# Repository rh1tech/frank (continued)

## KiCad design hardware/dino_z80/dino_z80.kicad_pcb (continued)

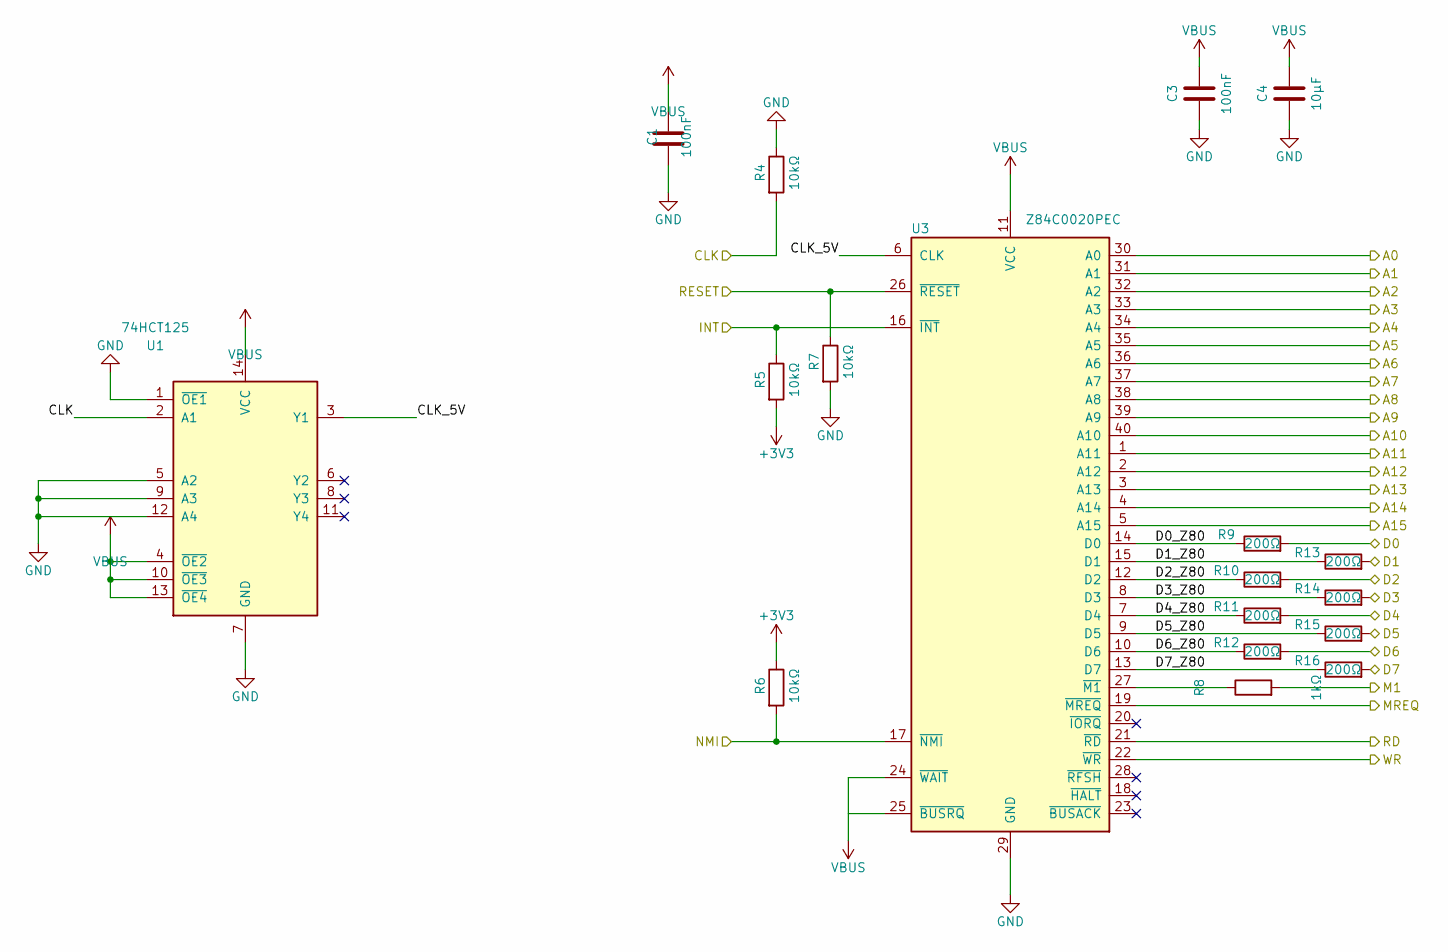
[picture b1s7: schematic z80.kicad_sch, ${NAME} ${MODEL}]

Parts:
C1, C3: 100nF; C_0603_1608Metric
C4: 10µF; C_0603_1608Metric
R4, R5, R6, R7: 10kΩ; R_0603_1608Metric
R8: 1kΩ; R_0603_1608Metric
R9, R10, R11, R12, R13, R14, R15, R16: 200Ω; R_0603_1608Metric
U1: 74HCT125; SOIC127P600X175-14N
U3: Z84C0020PEC; DIP-40_W15.24mm_Socket

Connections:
+3V3: R5.2, R6.1; also elsewhere on the board
/A0: U3.30 (A0); also elsewhere on the board
/A1: U3.31 (A1); also elsewhere on the board
/A2: U3.32 (A2); also elsewhere on the board
/A3: U3.33 (A3); also elsewhere on the board
/A4: U3.34 (A4); also elsewhere on the board
/A5: U3.35 (A5); also elsewhere on the board
/A6: U3.36 (A6); also elsewhere on the board
/A7: U3.37 (A7); also elsewhere on the board
/A8: U3.38 (A8); also elsewhere on the board
/A9: U3.39 (A9); also elsewhere on the board
/A10: U3.40 (A10); also elsewhere on the board
/A11: U3.1 (A11); also elsewhere on the board
/A12: U3.2 (A12); also elsewhere on the board
/A13: U3.3 (A13); also elsewhere on the board
/A14: U3.4 (A14); also elsewhere on the board
/A15: U3.5 (A15); also elsewhere on the board
/CLK: R4.2, U1.2 (A1); also elsewhere on the board
/D0: R9.2; also elsewhere on the board
/D1: R13.2; also elsewhere on the board
/D2: R10.2; also elsewhere on the board
/D3: R14.2; also elsewhere on the board
/D4: R11.2; also elsewhere on the board
/D5: R15.2; also elsewhere on the board
/D6: R12.2; also elsewhere on the board
/D7: R16.2; also elsewhere on the board
/INT: R5.1, U3.16 (~INT); also elsewhere on the board
/M1: R8.2; also elsewhere on the board
/MREQ: U3.19 (~MREQ); also elsewhere on the board
/NMI: R6.2, U3.17 (~NMI); also elsewhere on the board
/RD: U3.21 (~RD); also elsewhere on the board
/RESET: R7.1, U3.26 (~RESET); also elsewhere on the board
/WR: U3.22 (~WR); also elsewhere on the board
/Z80/CLK_5V: U1.3 (Y1), U3.6 (CLK)
/Z80/D0_Z80: R9.1, U3.14 (D0)
/Z80/D1_Z80: R13.1, U3.15 (D1)
/Z80/D2_Z80: R10.1, U3.12 (D2)
/Z80/D3_Z80: R14.1, U3.8 (D3)
/Z80/D4_Z80: R11.1, U3.7 (D4)
/Z80/D5_Z80: R15.1, U3.9 (D5)
/Z80/D6_Z80: R12.1, U3.10 (D6)
/Z80/D7_Z80: R16.1, U3.13 (D7)
GND: C1.2, C3.2, C4.2, R4.1, R7.2, U1.1 (~OE1), U1.5 (A2), U1.7 (GND), U1.9 (A3), U1.12 (A4), U3.29 (GND); also elsewhere on the board
unnamed: R8.1, U3.27 (~M1)
VBUS: C1.1, C3.1, C4.1, U1.4 (~OE2), U1.10 (~OE3), U1.13 (~OE4), U1.14 (VCC), U3.11 (VCC), U3.24 (~WAIT), U3.25 (~BUSRQ); also elsewhere on the board

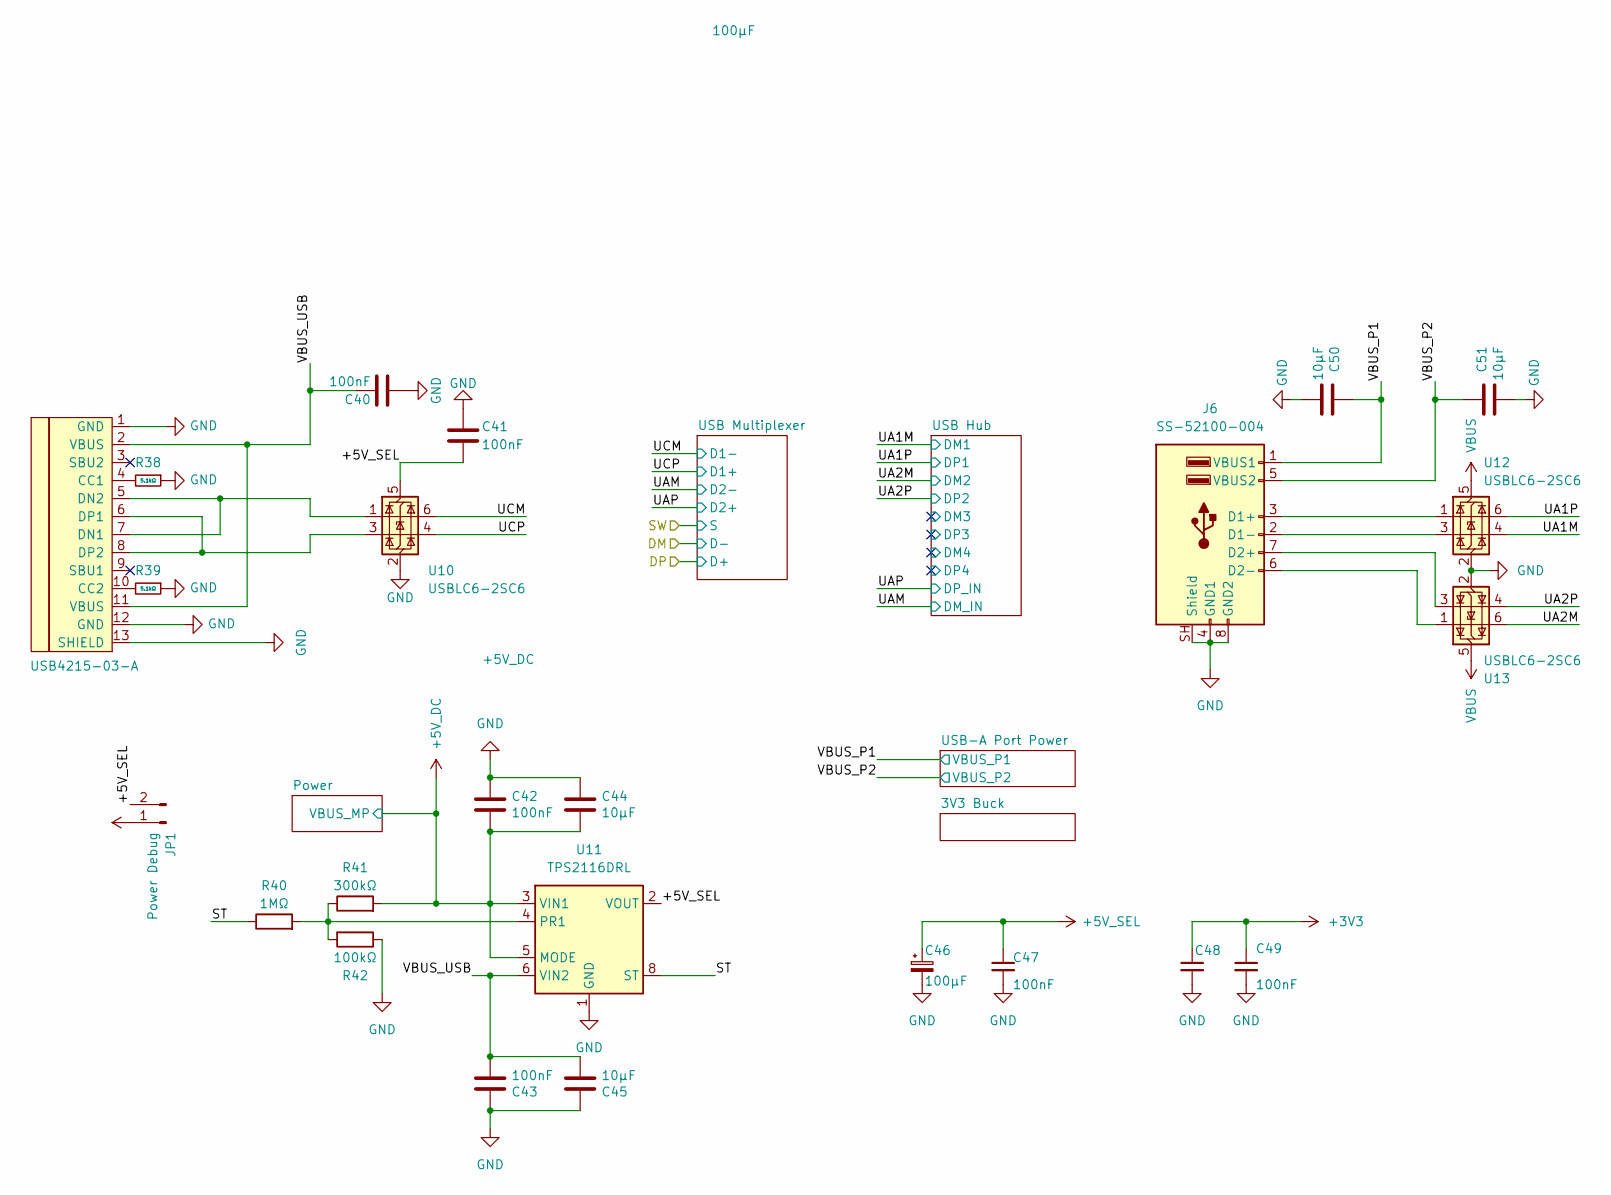
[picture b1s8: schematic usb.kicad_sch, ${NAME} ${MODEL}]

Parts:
C40, C41, C42, C43, C47, C49: 100nF; C_0603_1608Metric
C44, C45, C50, C51: 10µF; C_0603_1608Metric
C46: 100µF; CP_Radial_D6.3mm_P2.50mm
C48: 100µF; C_1206_3216Metric
J5: USB4215-03-A; USB_C_Receptacle; LCSC C165948
J6: SS-52100-004; USB_A_Stacked
JP1: Power Debug; SolderJumper-2_P1.3mm_Open_Pad1.0x1.5mm
R38, R39: 5.1kΩ; R_0603_1608Metric
R40: 1MΩ; R_0603_1608Metric
R41: 300kΩ; R_0603_1608Metric
R42: 100kΩ; R_0603_1608Metric
U10, U12, U13: USBLC6-2SC6; SOT-23-6
U11: TPS2116DRL; SOT-583-8

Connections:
+3V3: C48.1, C49.1; also elsewhere on the board
+5V_DC: C42.2, C44.2, JP1.1, R41.2, U11.3 (VIN1), U11.5 (MODE); also elsewhere on the board
+5V_SEL: C41.2, C46.1, C47.1, JP1.2, U10.5 (VBUS), U11.2 (VOUT), U11.7 (VOUT); also elsewhere on the board
/USB, Power/ST: R40.1, U11.8 (ST)
/USB, Power/UA1M: U12.4 (I/O2); also elsewhere on the board
/USB, Power/UA1P: U12.6 (I/O1); also elsewhere on the board
/USB, Power/UA2M: U13.6 (I/O1); also elsewhere on the board
/USB, Power/UA2P: U13.4 (I/O2); also elsewhere on the board
/USB, Power/UCM: U10.6 (I/O1); also elsewhere on the board
/USB, Power/UCP: U10.4 (I/O2); also elsewhere on the board
/USB, Power/VBUS_P1: C50.1, J6.1 (VBUS1); also elsewhere on the board
/USB, Power/VBUS_P2: C51.1, J6.5 (VBUS2); also elsewhere on the board
/USB, Power/VBUS_USB: C40.1, C43.2, C45.2, J5.2 (VBUS), J5.11 (VBUS), U11.6 (VIN2)
GND: C40.2, C41.1, C42.1, C43.1, C44.1, C45.1, C46.2, C47.2, C48.2, C49.2, C50.2, C51.2, J5.1 (GND), J5.12 (GND), J5.13 (SHIELD), J6.4 (GND1), J6.8 (GND2), J6.SH (Shield), R38.1, R39.1, R42.1, U10.2 (GND), U11.1 (GND), U12.2 (GND), U13.2 (GND); also elsewhere on the board
unnamed: J5.4 (CC1), R38.2
unnamed: J5.10 (CC2), R39.2
unnamed: J5.5 (DN2), J5.7 (DN1), U10.1 (I/O1)
unnamed: J5.6 (DP1), J5.8 (DP2), U10.3 (I/O2)
unnamed: J6.3 (D1+), U12.1 (I/O1)
unnamed: J6.2 (D1-), U12.3 (I/O2)
unnamed: J6.7 (D2+), U13.3 (I/O2)
unnamed: J6.6 (D2-), U13.1 (I/O1)
unnamed: R40.2, R41.1, R42.2, U11.4 (PR1)
VBUS: U12.5 (VBUS), U13.5 (VBUS); also elsewhere on the board

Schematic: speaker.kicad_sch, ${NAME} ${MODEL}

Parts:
C15: 6.8nF; C_0603_1608Metric
C16, C17: 1µF; C_0603_1608Metric
C18: 100nF; C_0603_1608Metric
C19: 10µF; C_0603_1608Metric
C20: 100µF; CP_Radial_D6.3mm_P2.50mm
LS1: CVS-2308
R25, R26: 22kΩ; R_0603_1608Metric
R27: 2kΩ; R_0603_1608Metric
R28, R29, R30: 10kΩ; R_0603_1608Metric
U6: PAM8403D; SOP-16_P1.27mm

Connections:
/Sound/AUDIO_L: R25.1; also elsewhere on the board
/Sound/AUDIO_R: R26.1; also elsewhere on the board
/Sound/SPK_EN: R30.1, U6.12 (SHDN); also elsewhere on the board
/Sound/Speaker/SPK_N: LS1.1 (-), U6.3 (-OUT_L)
/Sound/Speaker/SPK_P: LS1.2 (+), U6.1 (+OUT_L)
GND: C15.2, C17.2, C18.2, C19.2, C20.2, R27.2, R29.2, R30.2, U6.2 (PGND), U6.11 (GND), U6.15 (PGND); also elsewhere on the board
unnamed: C15.1, C16.1, R25.2, R26.2, R27.1
unnamed: C16.2, R28.1
unnamed: R28.2, U6.7 (INL)
unnamed: R29.1, U6.10 (INR)
unnamed: C17.1, U6.8 (VREF)
VBUS: C18.1, C19.1, C20.1, U6.4 (PVDD), U6.5 (MUTE), U6.6 (VDD), U6.13 (PVDD); also elsewhere on the board

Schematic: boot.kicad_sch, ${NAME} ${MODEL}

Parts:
S3: Boot; Button_SMD_3x4x2mm; Mouser Part Number 611-KMR221G-LFS

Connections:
/RP2350B/~USB_BOOT: S3.2, S3.4; also elsewhere on the board
GND: S3.1, S3.3; also elsewhere on the board

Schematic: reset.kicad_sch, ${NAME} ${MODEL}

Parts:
C52: 1nF; C_0603_1608Metric
S4: Reset; Button_SMD_3x4x2mm; Mouser Part Number 611-KMR221G-LFS

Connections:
/RP2350B/Reset/RESET: C52.2, S4.2, S4.4; also elsewhere on the board
GND: C52.1, S4.1, S4.3; also elsewhere on the board

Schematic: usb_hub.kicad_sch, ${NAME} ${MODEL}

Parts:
C9: 1µF; C_0603_1608Metric
C10: 4.7µF; C_0603_1608Metric; LCSC C1746
C11, C12: 100nF; C_0603_1608Metric
U5: MW7211A; SOIC127P600X175-16N

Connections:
/USB, Power/UA1M: U5.7 (DM3); also elsewhere on the board
/USB, Power/UA1P: U5.8 (DP3); also elsewhere on the board
/USB, Power/UA2M: U5.5 (DM2); also elsewhere on the board
/USB, Power/UA2P: U5.6 (DP2); also elsewhere on the board
/USB, Power/UAM: U5.10 (DMU); also elsewhere on the board
/USB, Power/UAP: U5.11 (DPU); also elsewhere on the board
/USB, Power/USB Hub/DM3: U5.3 (DM1)
/USB, Power/USB Hub/DM4: U5.1 (DM0)
/USB, Power/USB Hub/DP3: U5.4 (DP1)
/USB, Power/USB Hub/DP4: U5.2 (DP0)
/USB, Power/USB Hub/VD33: C9.1, C11.1, U5.12 (VD33), U5.14 (VD3)
GND: C9.2, C10.2, C11.2, C12.2, U5.15 (GND), U5.16 (GND); also elsewhere on the board
VBUS: C10.1, C12.1, U5.13 (VDD5); also elsewhere on the board

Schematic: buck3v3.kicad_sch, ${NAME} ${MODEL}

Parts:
C93, C94, C97: 10µF; C_0603_1608Metric
C95, C98: 100nF; C_0603_1608Metric
C96: 100µF; C_1206_3216Metric
C99: 22pF; C_0603_1608Metric
FB4: 330Ω@100MHz 2A; L_0805_2012Metric
L3: 2.2µH; L_Cenker_CKCS3015
R74: 100kΩ; R_0603_1608Metric
R75: 22kΩ; R_0603_1608Metric
TP10: +5V_BUCK; TestPoint_Pad_1.0x1.0mm
TP11: LX; TestPoint_Pad_1.0x1.0mm
U17: SY8089AAAC; SOT-23-5

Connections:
+3V3: C96.1, C97.1, C98.1, C99.1, L3.2, R74.1; also elsewhere on the board
/USB, Power/3V3 Buck/+5V_BUCK: C93.1, C94.1, C95.1, FB4.2, TP10.1 (1_1), U17.1 (EN), U17.4 (IN)
/USB, Power/3V3 Buck/FB: C99.2, R74.2, R75.1, U17.5 (FB)
GND: C93.2, C94.2, C95.2, C96.2, C97.2, C98.2, R75.2, U17.2 (GND); also elsewhere on the board
unnamed: L3.1, TP11.1 (1_1), U17.3 (LX)
VBUS: FB4.1; also elsewhere on the board

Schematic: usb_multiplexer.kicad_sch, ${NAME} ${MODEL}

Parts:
C2: 100nF; C_0603_1608Metric
R3: 10kΩ; R_0603_1608Metric
U2: TS3USB221RSER; Texas_R-PUQFN-N10

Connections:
+3V3: C2.2, U2.10 (VCC); also elsewhere on the board
/RP2350B/DM: U2.7 (D-); also elsewhere on the board
/RP2350B/DP: U2.8 (D+); also elsewhere on the board
/USB, Power/SW: R3.1, U2.9 (S); also elsewhere on the board
/USB, Power/UAM: U2.4 (2D-); also elsewhere on the board
/USB, Power/UAP: U2.3 (2D+); also elsewhere on the board
/USB, Power/UCM: U2.2 (1D-); also elsewhere on the board
/USB, Power/UCP: U2.1 (1D+); also elsewhere on the board
GND: C2.1, R3.2, U2.5 (GND), U2.6 (~OE); also elsewhere on the board

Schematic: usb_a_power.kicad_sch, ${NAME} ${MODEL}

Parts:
C100, C103: 100µF; CP_Radial_D6.3mm_P2.50mm
C101, C102: 10µF; C_0603_1608Metric
C104, C105: 100nF; C_0603_1608Metric
D6: Red; LED_0805_2012Metric_Pad1.15x1.40mm_HandSolder
R76, R77, R78: 100kΩ; R_0603_1608Metric
R79: 1kΩ; R_0603_1608Metric
U18, U19: CH217K; SOT-23-6

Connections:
/USB, Power/USB-A Port Power/USB_OC: D6.1 (K), R78.2, U18.3 (FLAG#), U19.3 (FLAG#)
/USB, Power/VBUS_P1: C105.1, U18.1 (VOUT); also elsewhere on the board
/USB, Power/VBUS_P2: C104.1, U19.1 (VOUT); also elsewhere on the board
GND: C100.2, C101.2, C102.2, C103.2, C104.2, C105.2, R76.2, R77.2, U18.2 (GND), U18.4 (EN#), U19.2 (GND), U19.4 (EN#); also elsewhere on the board
unnamed: D6.2 (A), R79.2
unnamed: R76.1, U18.5 (ISET)
unnamed: R77.1, U19.5 (ISET)
VBUS: C100.1, C101.1, C102.1, C103.1, R78.1, R79.1, U18.6 (VIN), U19.6 (VIN); also elsewhere on the board

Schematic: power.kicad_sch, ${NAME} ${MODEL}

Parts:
C53: 1µF; C_0603_1608Metric
C54: 680µF; CP_Radial_D8.0mm_P3.50mm
C55, C60: 10µF; C_0603_1608Metric
C56, C58, C59: 100nF; C_0603_1608Metric
C57: 150pF; C_0603_1608Metric
C61: 220µF; CP_Radial_D6.3mm_P2.50mm
D3: SS34; D_SMA
F1: 1.5A 24V; Fuse_1812_4532Metric
J7: DC-005-5A-2.0; BarrelJack_DC-005; PARTREV A0
JP2: Force On; SolderJumper-2_P1.3mm_Open_Pad1.0x1.5mm
L2: 22µH; Inductor_CDRH104RNP
Q1, Q2: AO3401A; SOT-23-3L_AOS
R43, R44, R45, R47, R49, R50: 100kΩ; R_0603_1608Metric
R46: 10kΩ; R_0603_1608Metric
R48: 39kΩ; R_0603_1608Metric
R51: 8.2kΩ; R_0603_1608Metric
R52: 43kΩ; R_0603_1608Metric
S5: SK12D07VG3NS; Switch_Slide_SK12D07VG3NS
TP2: +5V_DC; TestPoint_Pad_1.0x1.0mm
TP3: +5V_SEL; TestPoint_Pad_1.0x1.0mm
U14: MP1584EN-LF-Z; SOIC-9_P1.27mm; Mouser Part Number 946-MP1584ENLFZ

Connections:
+5V_DC: C59.2, C60.1, C61.1, L2.2, R52.1, TP2.1 (1_1); also elsewhere on the board
+5V_SEL: C53.1, Q2.2 (S), R43.1, TP3.1 (1_1); also elsewhere on the board
GND: C54.2, C55.2, C56.2, C59.1, C60.2, C61.2, D3.2 (A), J7.2, JP2.1 (A), R44.2, R48.2, R49.2, R50.2, R51.1, S5.2, U14.5 (GND), U14.9 (EP); also elsewhere on the board
unnamed: C57.2, R49.1
unnamed: C58.2, D3.1 (K), L2.1, U14.1 (SW)
unnamed: F1.1, J7.1
unnamed: JP2.2 (B), R46.2, S5.3
unnamed: F1.2, Q1.3 (D)
unnamed: Q1.1 (G), R44.1, R45.1
unnamed: C54.1, C55.1, C56.1, Q1.2 (S), R45.2, R47.2, U14.7 (VIN)
unnamed: C53.2, Q2.1 (G), R43.2, R46.1
unnamed: C58.1, U14.8 (BST)
unnamed: C57.1, U14.3 (COMP)
unnamed: R47.1, R48.1, U14.2 (EN)
unnamed: R51.2, R52.2, U14.4 (FB)
unnamed: R50.1, U14.6 (FREQ)
VBUS: Q2.3 (D); also elsewhere on the board

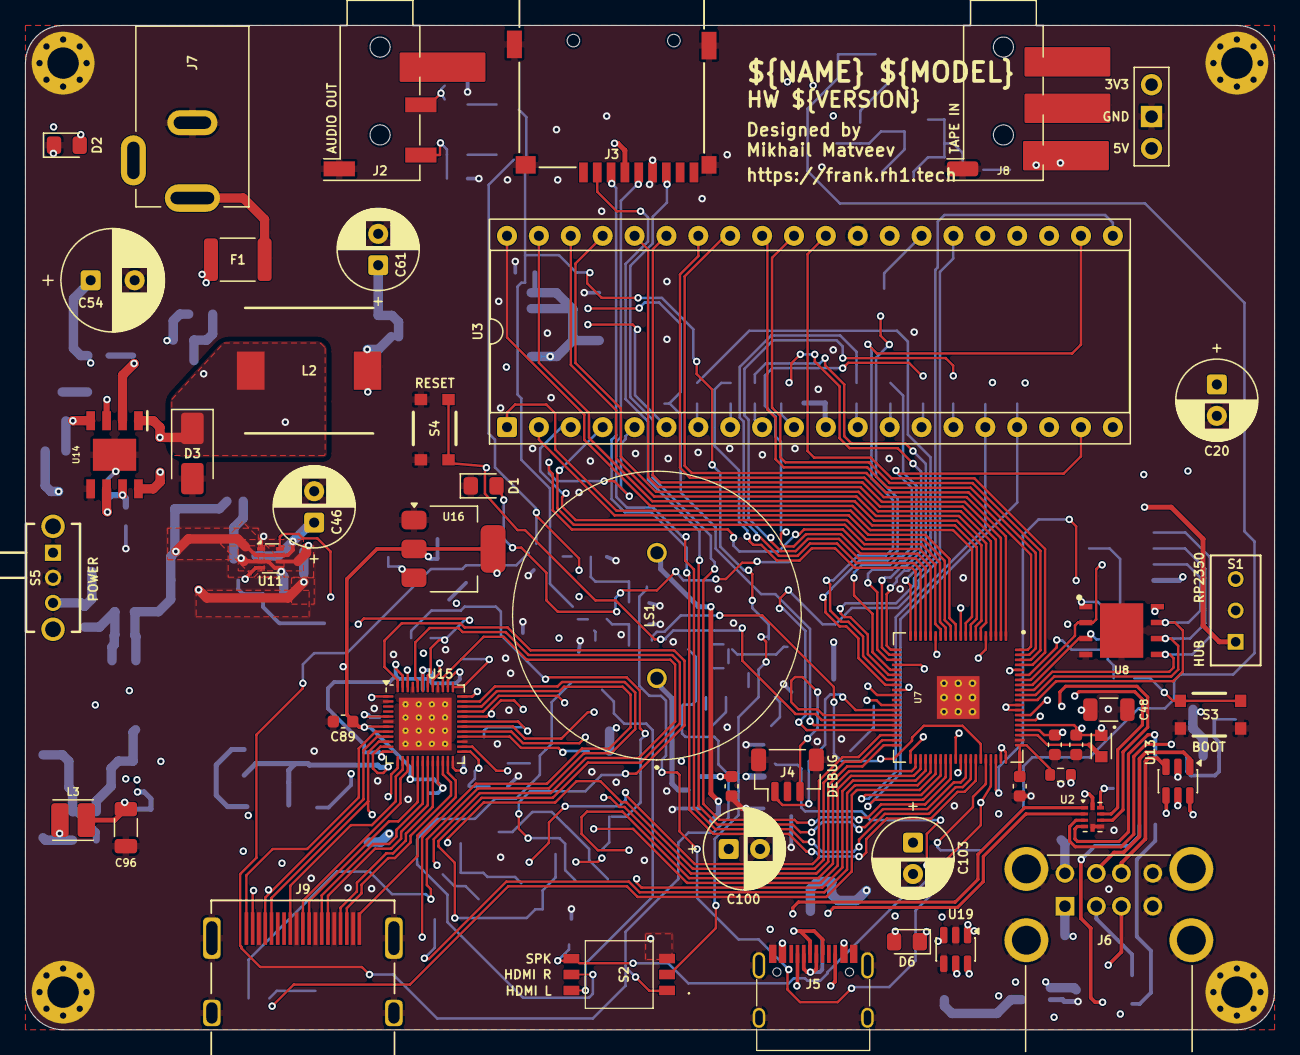
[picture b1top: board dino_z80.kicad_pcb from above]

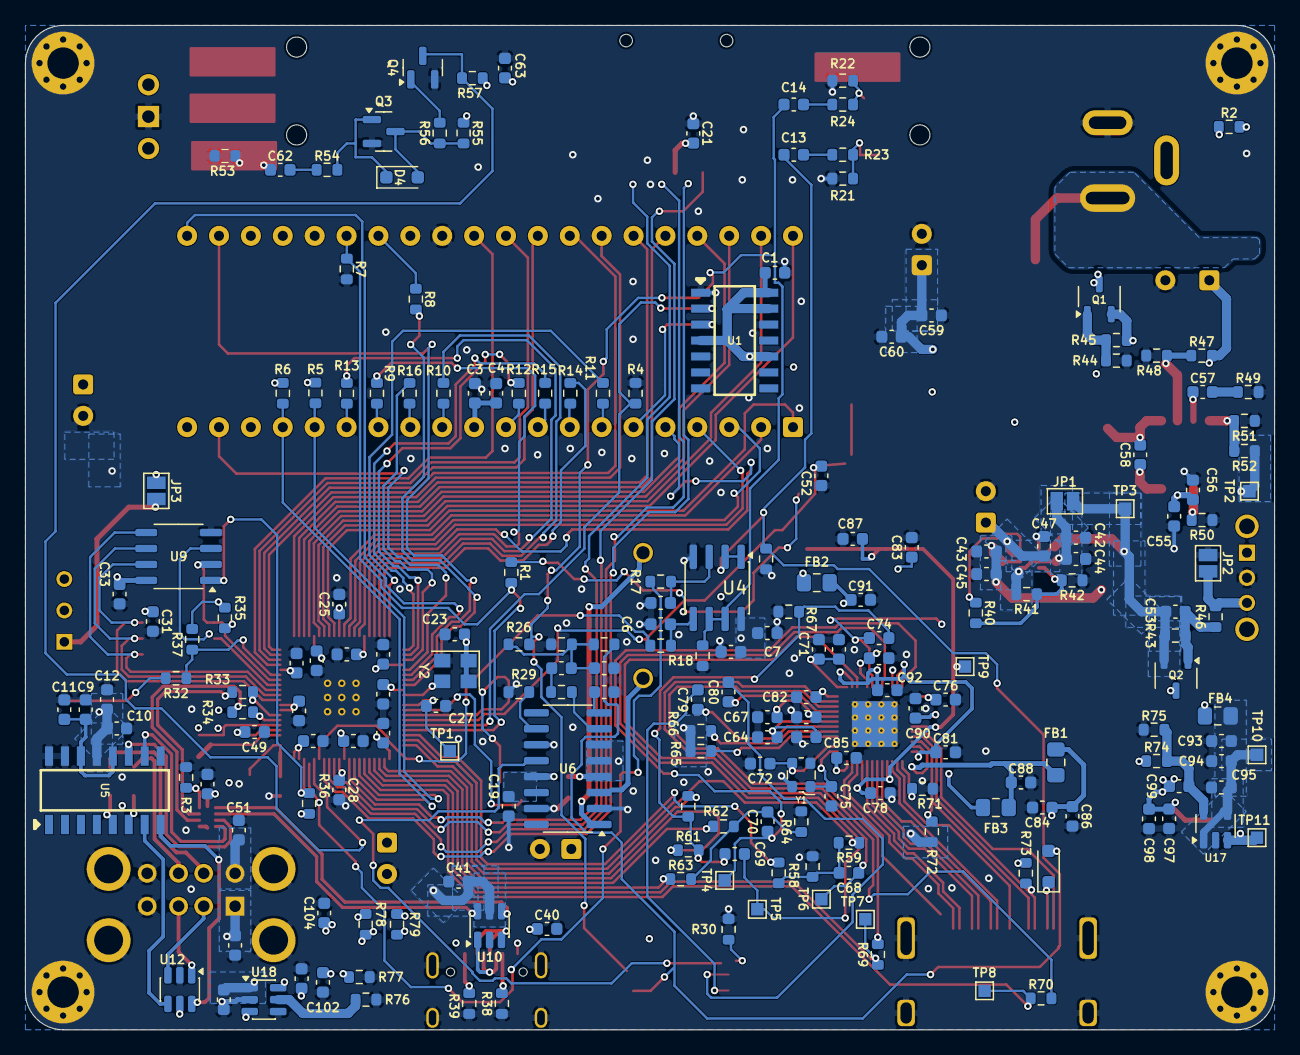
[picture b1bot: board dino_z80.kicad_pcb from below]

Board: 4 copper layers, 99.5 x 80.0 mm, 256 parts (205 on the bottom side), 185 nets.

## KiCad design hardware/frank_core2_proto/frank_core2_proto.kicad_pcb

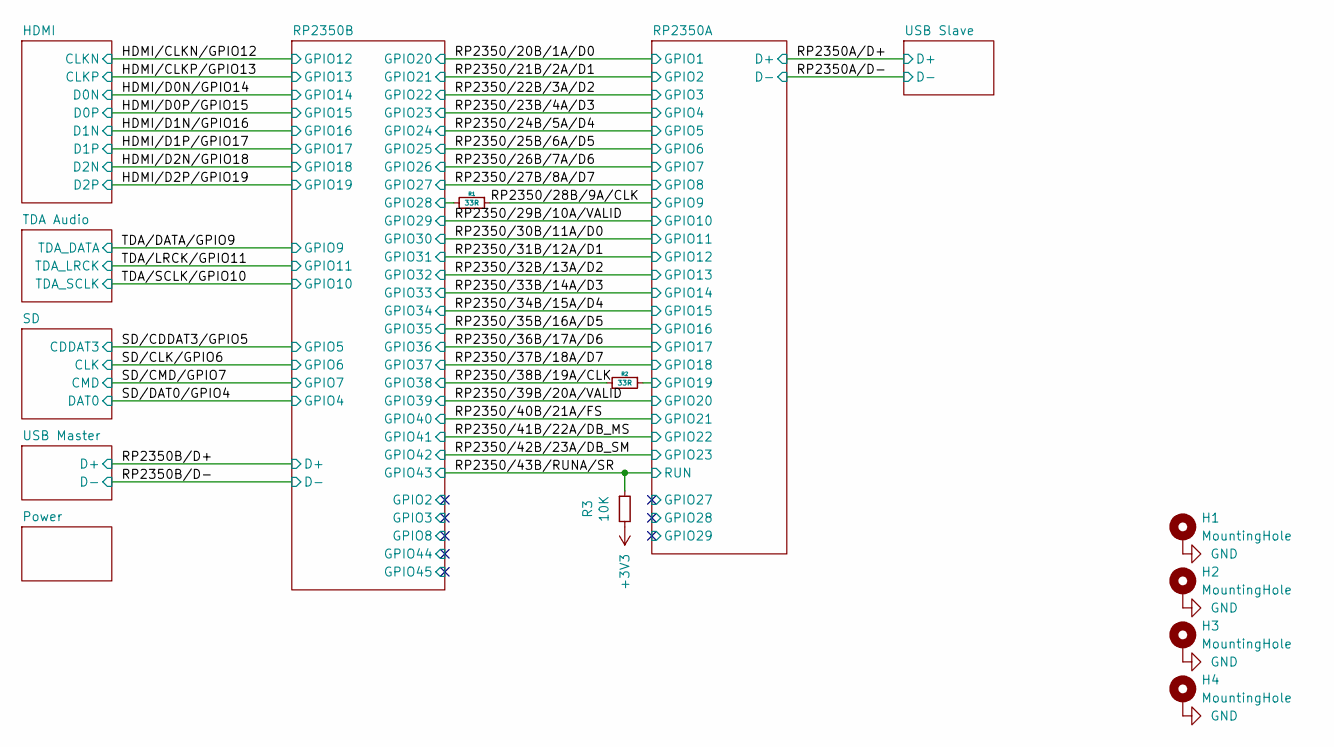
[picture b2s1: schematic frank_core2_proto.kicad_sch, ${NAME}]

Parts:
H1, H2, H3, H4: MountingHole; MountingHole_2.5mm_Pad_Via
R1, R2: 33R; R_0603_1608Metric
R3: 10K; R_0603_1608Metric

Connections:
+3V3: R3.2; also elsewhere on the board
/RP2350A/GPIO19: R2.1; also elsewhere on the board
/RP2350B/GPIO28: R1.2; also elsewhere on the board
/RP2350/28B/9A/CLK: R1.1; also elsewhere on the board
/RP2350/38B/19A/CLK: R2.2; also elsewhere on the board
/RP2350/43B/RUNA/SR: R3.1; also elsewhere on the board
GND: H1.1 (1_1), H2.1 (1_1), H3.1 (1_1), H4.1 (1_1); also elsewhere on the board

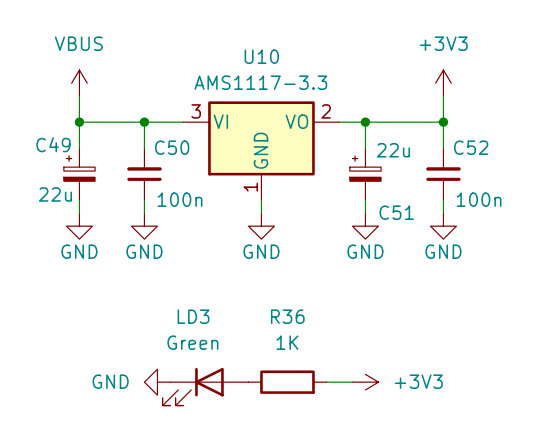
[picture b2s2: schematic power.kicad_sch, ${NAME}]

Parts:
C49, C51: 22u; CP_EIA-3528-12_Kemet-T
C50, C52: 100n; C_0603_1608Metric
LD3: Green; LED_0603_1608Metric
R36: 1K; R_0603_1608Metric
U10: AMS1117-3.3; SOT-89-3

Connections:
+3V3: C51.1, C52.2, R36.2, U10.2 (VO); also elsewhere on the board
GND: C49.2, C50.1, C51.2, C52.1, LD3.1 (K), U10.1 (GND); also elsewhere on the board
unnamed: LD3.2 (A), R36.1
VBUS: C49.1, C50.2, U10.3 (VI); also elsewhere on the board

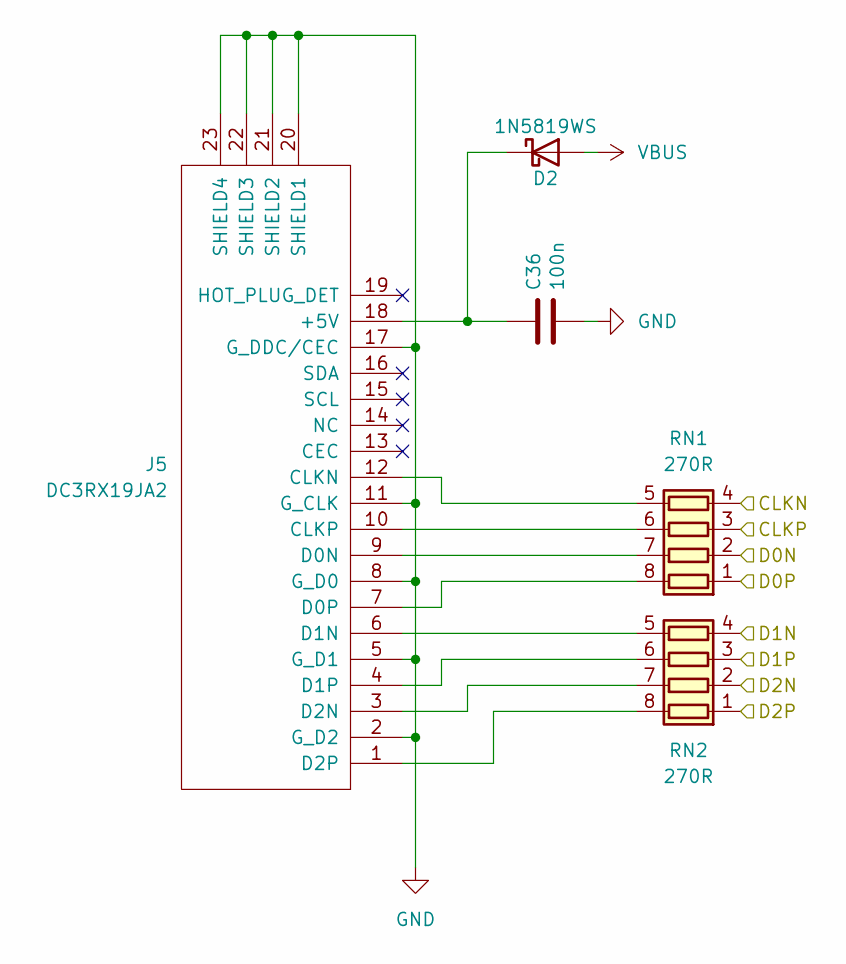
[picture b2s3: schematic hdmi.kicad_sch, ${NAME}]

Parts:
C36: 100n; C_0603_1608Metric
D2: 1N5819WS; D_SOD-323
J5: DC3RX19JA2; HDMI_Female
RN1, RN2: 270R; R_Array_4x0603

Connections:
/HDMI/CLKN/GPIO12: RN1.4 (R4.1); also elsewhere on the board
/HDMI/CLKP/GPIO13: RN1.3 (R3.1); also elsewhere on the board
/HDMI/D0N/GPIO14: RN1.2 (R2.1); also elsewhere on the board
/HDMI/D0P/GPIO15: RN1.1 (R1.1); also elsewhere on the board
/HDMI/D1N/GPIO16: RN2.4 (R4.1); also elsewhere on the board
/HDMI/D1P/GPIO17: RN2.3 (R3.1); also elsewhere on the board
/HDMI/D2N/GPIO18: RN2.2 (R2.1); also elsewhere on the board
/HDMI/D2P/GPIO19: RN2.1 (R1.1); also elsewhere on the board
GND: C36.2, J5.2 (G_D2), J5.5 (G_D1), J5.8 (G_D0), J5.11 (G_CLK), J5.17 (G_DDC/CEC), J5.20 (SHIELD1), J5.21 (SHIELD2), J5.22 (SHIELD3), J5.23 (SHIELD4); also elsewhere on the board
unnamed: C36.1, D2.1 (K), J5.18 (+5V)
unnamed: J5.12 (CLKN), RN1.5 (R4.2)
unnamed: J5.10 (CLKP), RN1.6 (R3.2)
unnamed: J5.9 (D0N), RN1.7 (R2.2)
unnamed: J5.7 (D0P), RN1.8 (R1.2)
unnamed: J5.6 (D1N), RN2.5 (R4.2)
unnamed: J5.4 (D1P), RN2.6 (R3.2)
unnamed: J5.3 (D2N), RN2.7 (R2.2)
unnamed: J5.1 (D2P), RN2.8 (R1.2)
VBUS: D2.2 (A); also elsewhere on the board

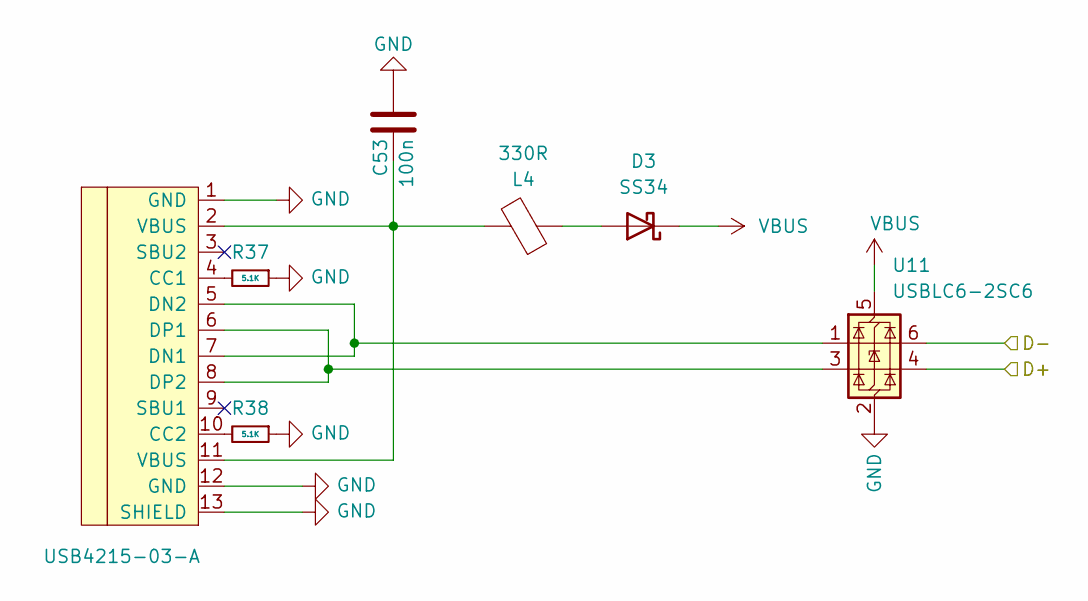
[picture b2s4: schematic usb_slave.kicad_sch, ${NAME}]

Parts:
C53: 100n; C_0603_1608Metric
D3: SS34; D_SMA
J9: USB4215-03-A; USB_C_Receptacle; LCSC C165948
L4: 330R; L_0603_1608Metric
R37, R38: 5.1K; R_0603_1608Metric
U11: USBLC6-2SC6; SOT-23-6

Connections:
/RP2350A/D+: U11.4 (I/O2); also elsewhere on the board
/RP2350A/D-: U11.6 (I/O1); also elsewhere on the board
GND: C53.2, J9.1 (GND), J9.12 (GND), J9.13 (SHIELD), R37.1, R38.1, U11.2 (GND); also elsewhere on the board
unnamed: C53.1, J9.2 (VBUS), J9.11 (VBUS), L4.2
unnamed: D3.2 (A), L4.1
unnamed: J9.4 (CC1), R37.2
unnamed: J9.10 (CC2), R38.2
unnamed: J9.5 (DN2), J9.7 (DN1), U11.1 (I/O1)
unnamed: J9.6 (DP1), J9.8 (DP2), U11.3 (I/O2)
VBUS: D3.1 (K), U11.5 (VBUS); also elsewhere on the board
